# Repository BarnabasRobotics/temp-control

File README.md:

# temp-control
Arduino-based temperature display and controller -- Created by Ling Leng

Revision History:
12/27/2017
- Added first version "Bare Bones Arduino.zip"
- Replaced "Bare Bones Arduino.zip" with new "TempControl V1.0" files which only includes .brd and .sch files
- Added Mini USB power supply part
- Added external oscillator
- Removed ISP-6 header
- Added reset button
- Added voltage regulator circuit

1/1/2018
- Added OLED
- Added .lbr file

1/2/2018
- Created new TempControl.lbr
- Created parts list
- Went through every parts and replaced them with TempControl.lbr
- Replaced ams1117 with L7805C
- Replaced the reset button
- Removed two LEDs
- Changed packages fot some capacitors
- Added frame

1/3/2018
- For U2, Added 0.33uF on Pin1 and 0.1uF on Pin3
- For U1, Added 0.1uF on Pin7 and 1.0uF on Pin20
- Added Diode on Pin1 for J3, Power Pin for J1, and VCC Pin for J4
- Added Green LED as power indicator
- Added a 4-PIN connector for OLED
- Rearranged and Rerouted the whole board

1/8/2018
- Removed power jack
- Removed 5V regulator
- Added 3v regulator
- Added level shifter

1/19/2018
- Added temp sensor

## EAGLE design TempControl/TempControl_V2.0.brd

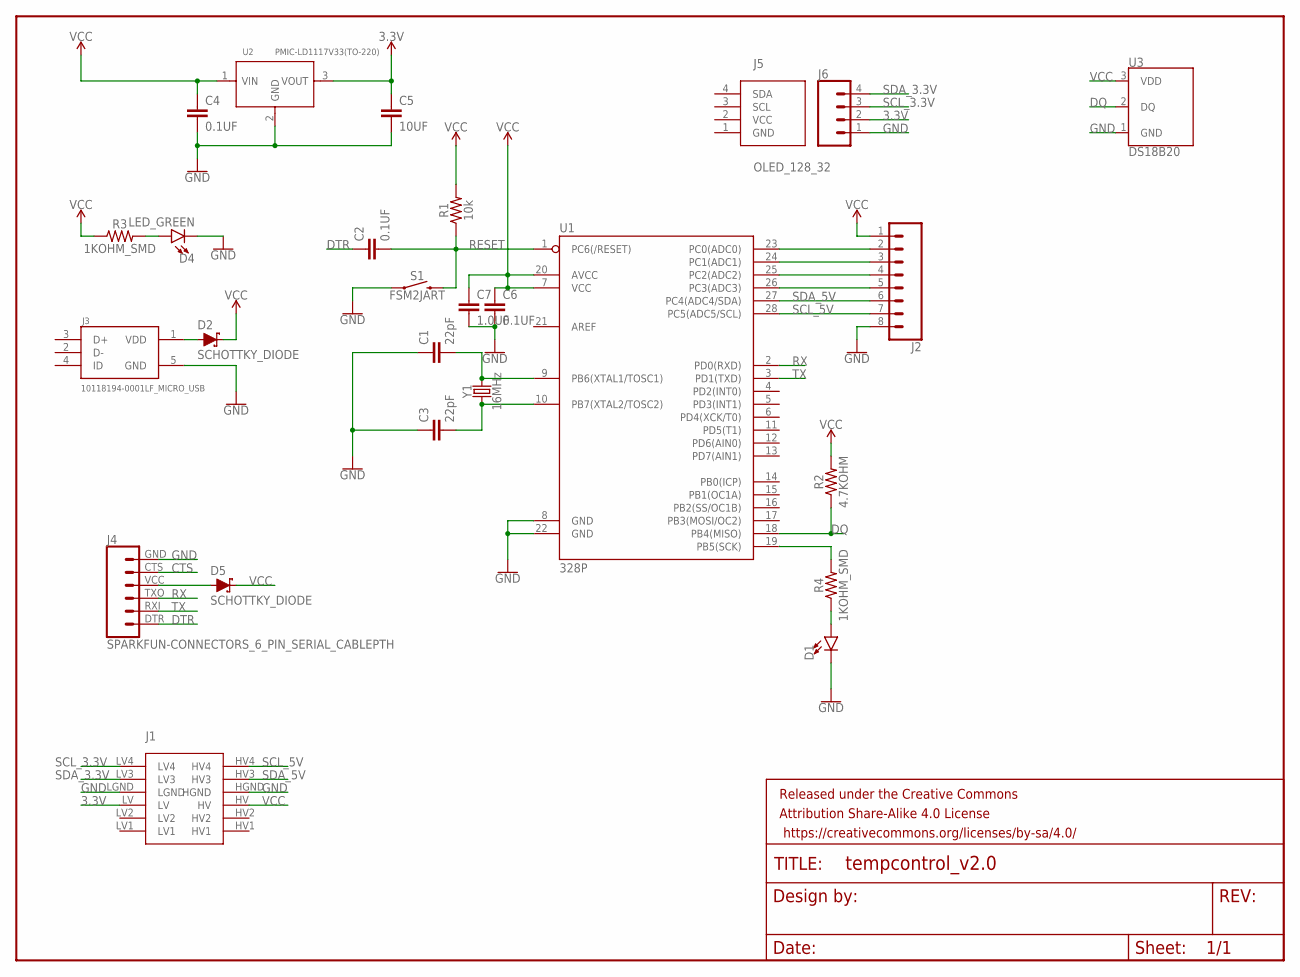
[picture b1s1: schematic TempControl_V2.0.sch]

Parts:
C1, C3: 22pF; CAP-PTH-2.54
C2, C4, C6: 0.1UF; CAP-PTH-2.54
C5: 10UF; CAP-PTH-5MM
C7: 1.0UF; CAP-PTH-5MM
D1: LED_RED5MM; LED_5MM
D2, D5: SCHOTTKY_DIODE; DIODE_0805
D4: LED_GREEN; LED-0603
FRAME1: FRAME-LETTERNO_PACKAGE; DUMMY
J1: LEVEL_SHIFTER
J2: SPARKFUN-CONNECTORS_CONN_08"; SPARKFUN-CONNECTORS_1X08
J3: 10118194-0001LF_MICRO_USB; FRAMATOME_10118194-0001LF
J4: SPARKFUN-CONNECTORS_6_PIN_SERIAL_CABLEPTH; SPARKFUN-CONNECTORS_FTDI_BASIC
J5: OLED_128_32
J6: CONN_04; 1X04
R1: 10k; AXIAL-0.3
R2: 4.7KOHM; AXIAL-0.3
R3, R4: 1KOHM_SMD; 0603
S1: FSM2JART
U1: 328P; DIP28
U2: PMIC-LD1117V33(TO-220); TO-220
U3: DS18B20; TO-92-AMMO
Y1: 16MHz; HC49US

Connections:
3.3V: C5.1, J1.LV, J6.2, U2.3 (VOUT)
CTS: J4.CTS (5)
DQ: R2.P$1 (1), U1.18 (PB4(MISO)), U3.2 (DQ)
DTR: C2.1, J4.DTR (1)
GND: C1.1, C3.1, C4.2, C5.2, C6.2, C7.2, D1.K (2), D4.2, J1.HGND, J1.LGND, J2.8, J3.5 (GND), J4.GND (6), J6.1, S1.1, U1.8 (GND), U1.22 (GND), U2.2 (GND), U3.1 (GND)
unnamed: J2.2, U1.23 (PC0(ADC0))
unnamed: J2.3, U1.24 (PC1(ADC1))
unnamed: J2.4, U1.25 (PC2(ADC2))
unnamed: J2.5, U1.26 (PC3(ADC3))
unnamed: C1.2, U1.9 (PB6(XTAL1/TOSC1)), Y1.2
unnamed: R4.2, U1.19 (PB5(SCK))
unnamed: D2.1, J3.1 (VDD)
unnamed: D1.A (1), R4.1
unnamed: D4.1, R3.2
unnamed: C3.2, U1.10 (PB7(XTAL2/TOSC2)), Y1.1
unnamed: D5.1, J4.VCC (4)
RESET: C2.2, R1.P$1 (1), S1.2, U1.1 (PC6(/RESET))
RX: J4.TXO (3), U1.2 (PD0(RXD))
SCL_3.3V: J1.LV4, J6.3
SCL_5V: J1.HV4, J2.7, U1.28 (PC5(ADC5/SCL))
SDA_3.3V: J1.LV3, J6.4
SDA_5V: J1.HV3, J2.6, U1.27 (PC4(ADC4/SDA))
TX: J4.RXI (2), U1.3 (PD1(TXD))
VCC: C4.1, C6.1, C7.1, D2.2, D5.2, J1.HV, J2.1, R1.P$2 (2), R2.P$2 (2), R3.1, U1.7 (VCC), U1.20 (AVCC), U2.1 (VIN), U3.3 (VDD)

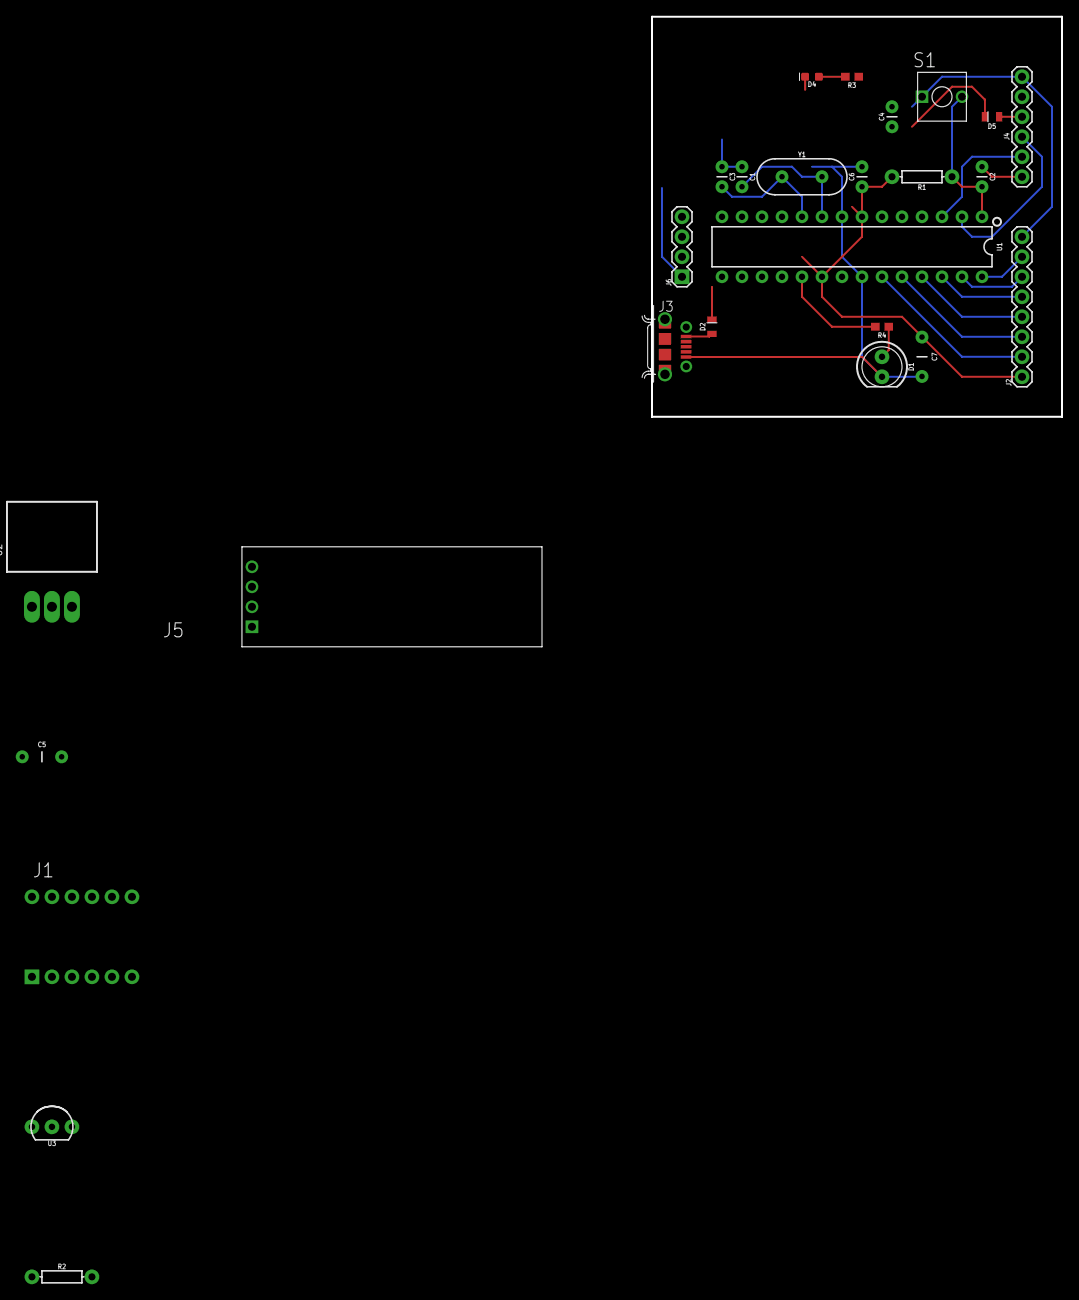
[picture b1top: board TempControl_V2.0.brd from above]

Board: 2 copper layers, 52.1 x 50.8 mm, 27 parts (0 on the bottom side), 23 nets.

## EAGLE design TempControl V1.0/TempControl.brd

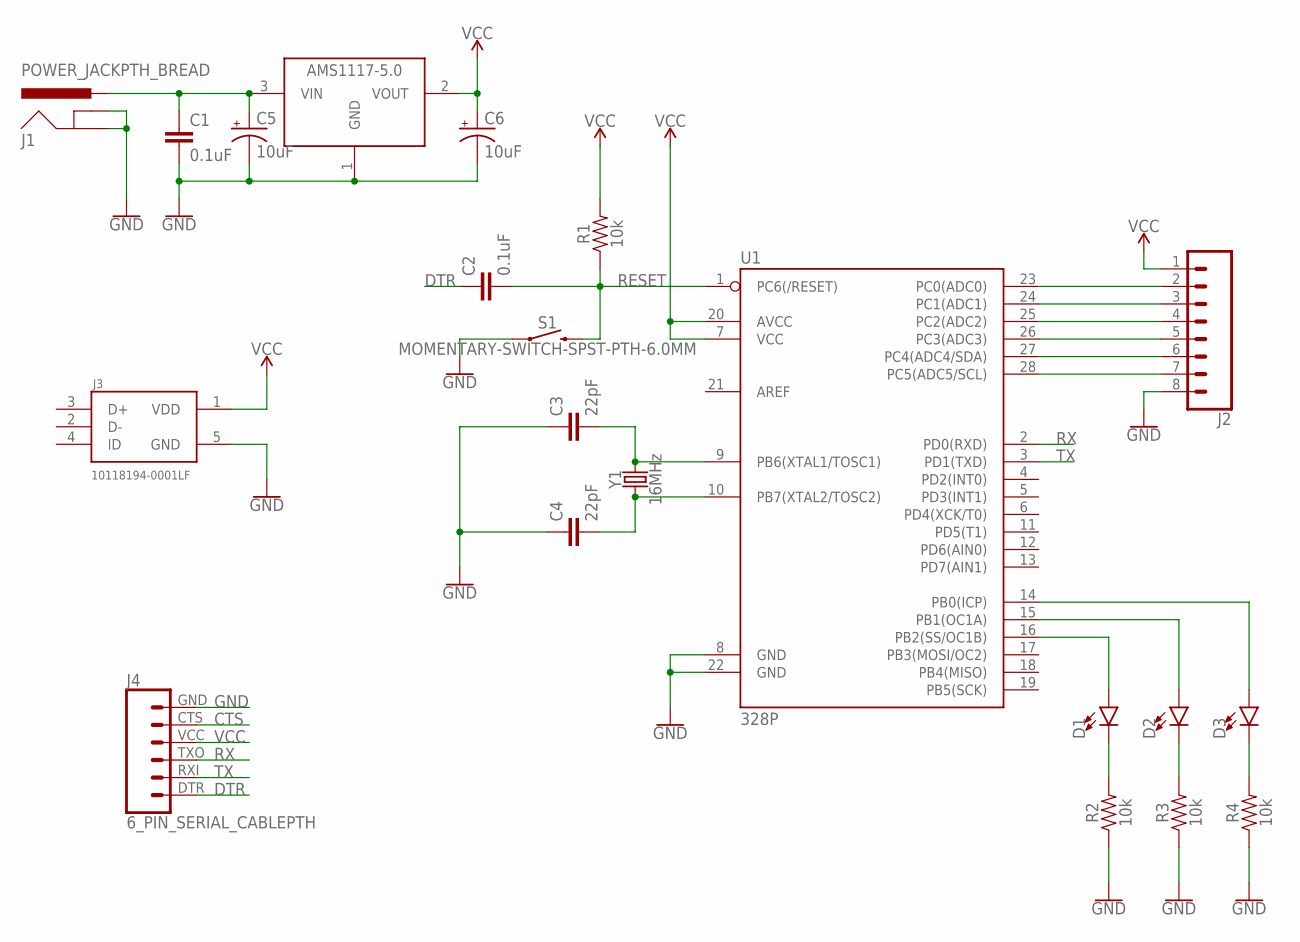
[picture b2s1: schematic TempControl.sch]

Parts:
C1, C2: 0.1uF; CAP-PTH-SMALL-KIT
C3, C4: 22pF; CAP-PTH-2.54
C5, C6: 10uF; CPOL-RADIAL-2.5MM-5MM
D1, D2, D3: LED5MM; LED_5MM
J1: POWER_JACKPTH_BREAD; POWER_JACK_PTH_BREAD
J2: CONN_08"; 1X08
J3: 10118194-0001LF; FRAMATOME_10118194-0001LF
J4: 6_PIN_SERIAL_CABLEPTH; FTDI_BASIC
R1, R2, R3, R4: 10k; AXIAL-0.3
S1: MOMENTARY-SWITCH-SPST-PTH-6.0MM; TACTILE_SWITCH_PTH_6.0MM
U1: 328P; DIP28
U$1: AMS1117-5.0; SOT223
Y1: 16MHz; HC49US

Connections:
CTS: J4.CTS (5)
DTR: C2.1, J4.DTR (1)
GND: C1.2, C3.1, C4.1, C5.2 (-), C6.2 (-), J1.GND, J1.GNDBREAK, J2.8, J3.5 (GND), J4.GND (6), R2.P$1 (1), R3.P$1 (1), R4.P$1 (1), S1.1, U1.8 (GND), U1.22 (GND), U$1.1 (GND)
unnamed: J2.2, U1.23 (PC0(ADC0))
unnamed: J2.3, U1.24 (PC1(ADC1))
unnamed: J2.4, U1.25 (PC2(ADC2))
unnamed: J2.5, U1.26 (PC3(ADC3))
unnamed: J2.6, U1.27 (PC4(ADC4/SDA))
unnamed: J2.7, U1.28 (PC5(ADC5/SCL))
unnamed: C3.2, U1.9 (PB6(XTAL1/TOSC1)), Y1.2
unnamed: D3.A, U1.14 (PB0(ICP))
unnamed: D2.A, U1.15 (PB1(OC1A))
unnamed: D1.A, U1.16 (PB2(SS/OC1B))
unnamed: D3.K (C), R4.P$2 (2)
unnamed: D2.K (C), R3.P$2 (2)
unnamed: D1.K (C), R2.P$2 (2)
unnamed: C4.2, U1.10 (PB7(XTAL2/TOSC2)), Y1.1
unnamed: C1.1, C5.1 (+), J1.PWR, U$1.3 (VIN)
RESET: C2.2, R1.P$1 (1), S1.3 (2), U1.1 (PC6(/RESET))
RX: J4.TXO (3), U1.2 (PD0(RXD))
TX: J4.RXI (2), U1.3 (PD1(TXD))
VCC: C6.1 (+), J2.1, J3.1 (VDD), J4.VCC (4), R1.P$2 (2), U1.7 (VCC), U1.20 (AVCC), U$1.2 (VOUT)

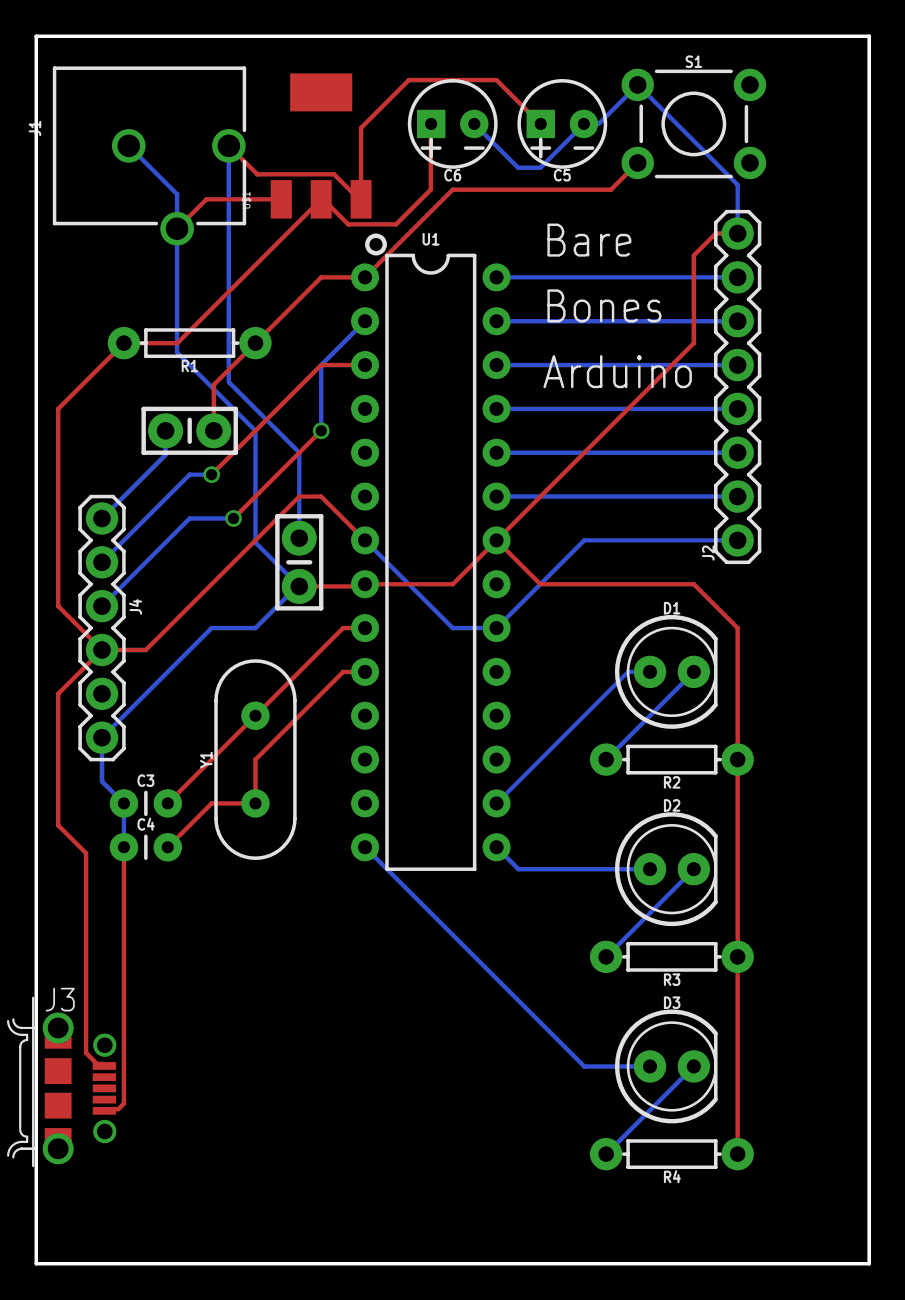
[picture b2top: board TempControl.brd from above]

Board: 2 copper layers, 48.3 x 71.1 mm, 21 parts (0 on the bottom side), 21 nets.

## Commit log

2017-12-27 Eagle Files
    Include Schematic and PCB Layout
2017-12-28 Delete Bare Bones Arduino.zip
    Replace it with new TempControl files
2017-12-28 Update new eagle files
    .brd and .sch for TempControl V1.0
2018-01-02 - Added .lbr file for TempControl project - Added OLED part - Rename the project name
2018-01-03 A lot of changes happened
    - Added new TempControl.lbr
    - Added parts list
    - Modified and added many parts
    - Redesigned the board
2018-01-19 - updated schematic and layout
    - removed power jack
    - added 3.3V regulator
    - added OLED
    - added level shifter
    - added temp sensor

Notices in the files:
parts and their libraries:
SparkFun-Capacitors: Licensing: Creative Commons ShareAlike 4.0 International - https://creativecommons.org/licenses/by-sa/4.0
TempControl: Released under the Creative Commons Attribution Share-Alike 4.0 License
TempControl: https://creativecommons.org/licenses/by-sa/4.0
